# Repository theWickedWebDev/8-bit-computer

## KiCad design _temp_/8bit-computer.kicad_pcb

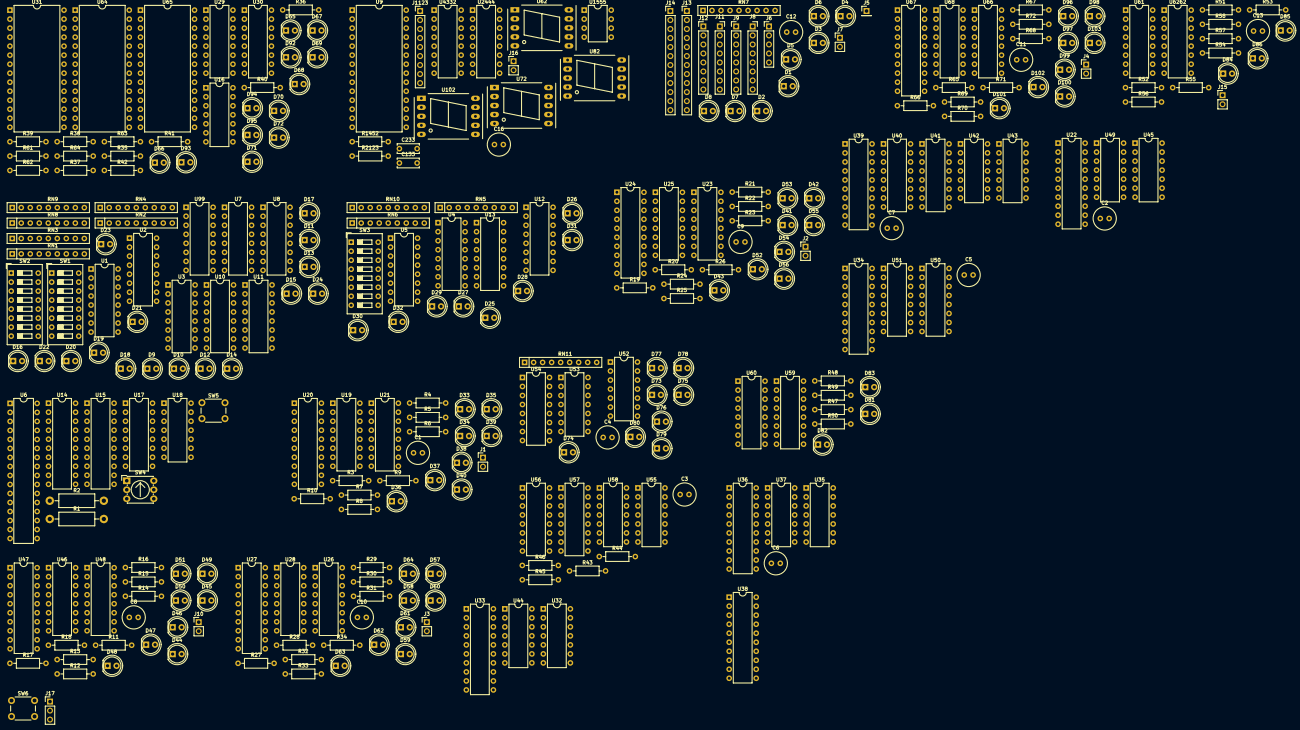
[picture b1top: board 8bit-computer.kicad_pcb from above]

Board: 2 copper layers, 296 parts (0 on the bottom side), 467 nets, no tracks yet.

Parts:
C1, C2, C3, C4, C5, C6, C7, C8, C9, C10, C11, C12, C13, C16: CP1; C_Radial_D6.3mm_H11.0mm_P2.50mm
C133: CP; C_Disc_D6.0mm_W2.5mm_P5.00mm
C233: C; C_Disc_D6.0mm_W2.5mm_P5.00mm
D1, D2, D3, D4, D5, D6, D7, D8, D9, D10, D11, D12, D13, D14, D15, D16, D17, D18, D19, D20, D21, D22, D23, D24, D25, D26, D27, D28, D29, D30, D31, D32, D33, D34, D35, D36, D37, D38, D39, D40, D41, D42, D43, D44, D45, D46, D47, D48, D49, D50, D51, D52, D53, D54, D55, D56, D57, D58, D59, D60, D61, D62, D63, D64, D65, D66, D67, D68, D69, D70, D71, D72, D73, D74, D75, D76, D77, D78, D79, D80, D81, D82, D83, D84, D85, D86, D92, D93, D94, D95, D96, D97, D98, D99, D100, D101, D102, D103: LED; LED_D5.0mm
J1, J2, J3, J4, J7, J10, J15, J16: Conn_01x04; PinHeader_1x02_P2.54mm_Vertical
J5: Conn_01x04; PinHeader_1x01_P2.54mm_Vertical
J6: Conn_01x04; PinHeader_1x05_P2.54mm_Vertical
J8, J11: Conn_01x08; PinSocket_1x08_P2.54mm_Vertical
J9, J12: Conn_01x08; PinHeader_1x08_P2.54mm_Vertical
J13, J14: Conn_01x08; PinHeader_1x12_P2.54mm_Vertical
J17: Conn_01x03; PinHeader_1x03_P2.54mm_Vertical
J1123: Conn_01x09; PinHeader_1x09_P2.54mm_Vertical
R1, R2: R_US; R_Axial_DIN0411_L9.9mm_D3.6mm_P15.24mm_Horizontal
R3, R4, R5, R6, R7, R8, R9, R10, R11, R12, R13, R14, R15, R16, R17, R18, R19, R20, R21, R22, R23, R24, R25, R26, R27, R28, R29, R30, R31, R32, R33, R34, R35, R36, R37, R38, R39, R40, R41, R42, R43, R44, R45, R46, R47, R48, R49, R50, R51, R52, R53, R54, R55, R56, R57, R58, R61, R62, R63, R64, R65, R66, R67, R68, R69, R70, R71, R72, R1452, R2123: R_US; R_Axial_DIN0207_L6.3mm_D2.5mm_P10.16mm_Horizontal
RN1, RN2, RN3, RN4, RN5, RN6, RN8, RN9, RN10: R_Network08_US; R_Array_SIP9
RN7, RN11: R_Network08; R_Array_SIP9
SW1, SW2, SW3: SW_DIP_x08; SW_DIP_SPSTx08_Slide_9.78x22.5mm_W7.62mm_P2.54mm
SW4: SW_SPDT; Nidec_Copal_SH-7010C
SW5, SW6: SW_Push; SW_PUSH_6mm
U1, U2, U4, U5, U7, U10, U19, U21, U23, U25, U26, U28, U66, U68: 74LS173; DIP-16_W7.62mm
U3, U8, U11, U12, U13, U17, U56, U57, U99: 74LS157; DIP-16_W7.62mm
U6: IS61C1024-15N; DIP-32_W7.62mm
U9, U31, U64, U65: AT28C256; DIP-28_W15.24mm
U14, U15, U20, U22, U24, U27, U33, U34, U36, U38, U39, U47, U67: 74LS245; DIP-20_W7.62mm
U16, U52, U55, U58: 74LS04; DIP-14_W7.62mm
U18: 74LS00; DIP-14_W7.62mm
U29, U46, U48: 74LS161; DIP-16_W7.62mm
U30, U54: 74LS138; DIP-16_W7.62mm
U32, U44, U53: 74LS08; DIP-14_W7.62mm
U35, U37, U42, U43: 74LS86; DIP-14_W7.62mm
U40, U41: 74LS283; DIP-16_W7.62mm
U45, U49: 74LS32; DIP-14_W7.62mm
U50, U51: 74LS194; DIP-16_W7.62mm
U59, U60: 74LS85; DIP-16_W7.62mm
U61, U6262: 74LS08; DIP-16_W7.62mm
U62, U72, U82, U102: HDSP-7503; 7SegmentLED_LTS6760_LTS6780
U1555: NE55P; DIP-8_W7.62mm
U2444: 74LS76; DIP-16_W7.62mm
U4332: 74LS139; DIP-16_W7.62mm

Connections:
+5V: R1.1, R2.2, RN1.1, RN2.1, RN3.1, RN4.1, RN6.1, U1.16, U2.16, U3.16, U4.16, U5.16, U6.30, U6.32, U7.16, U8.16, U10.16, U11.16, U12.16, U13.16, U14.20, U15.20, U17.16, U99.16
/ALU Arithmetic Logic Unit/A1: J8.8, J9.8, U37.13, U38.11, U41.5, U44.1, U49.12, U51.6, U59.10
/ALU Arithmetic Logic Unit/A2: J8.7, J9.7, U37.10, U38.12, U41.3, U44.4, U49.9, U51.5, U59.12
/ALU Arithmetic Logic Unit/A3: J8.6, J9.6, U37.5, U38.13, U41.14, U44.9, U49.4, U51.4, U59.13
/ALU Arithmetic Logic Unit/A4: J8.5, J9.5, U37.2, U38.14, U41.12, U44.12, U49.1, U51.3, U59.15
/ALU Arithmetic Logic Unit/A5: J8.4, J9.4, U32.1, U35.13, U38.15, U40.5, U45.12, U50.6, U60.10
/ALU Arithmetic Logic Unit/A6: J8.3, J9.3, U32.4, U35.10, U38.16, U40.3, U45.9, U50.5, U60.12
/ALU Arithmetic Logic Unit/A7: J8.2, J9.2, U32.9, U35.5, U38.17, U40.14, U45.4, U50.4, U60.13
/ALU Arithmetic Logic Unit/A8: J8.1, J9.1, U32.12, U35.2, U38.18, U40.12, U45.1, U50.3, U60.15
/ALU Arithmetic Logic Unit/ALU Control Pins/ADD: U39.19, U53.3
/ALU Arithmetic Logic Unit/ALU Control Pins/AND: D77.2, U33.19, U54.12
/ALU Arithmetic Logic Unit/ALU Control Pins/EN: J6.2, U54.6
/ALU Arithmetic Logic Unit/ALU Control Pins/F0: J6.5, U54.1
/ALU Arithmetic Logic Unit/ALU Control Pins/F1: J6.4, U54.2
/ALU Arithmetic Logic Unit/ALU Control Pins/F2: J6.3, U54.3
/ALU Arithmetic Logic Unit/ALU Control Pins/SHIFT_EN: U34.19, U53.6
/ALU Arithmetic Logic Unit/ALU Control Pins/SHL: D75.2, U50.10, U51.10, U53.4, U54.10
/ALU Arithmetic Logic Unit/ALU Control Pins/SHR: D74.2, U50.9, U51.9, U53.5, U54.9
/ALU Arithmetic Logic Unit/B1: J11.8, J12.8, U37.12, U43.12, U44.2, U49.13, U59.9
/ALU Arithmetic Logic Unit/B2: J11.7, J12.7, U37.9, U43.9, U44.5, U49.10, U59.11
/ALU Arithmetic Logic Unit/B3: J11.6, J12.6, U37.4, U43.4, U44.10, U49.5, U59.14
/ALU Arithmetic Logic Unit/B4: J11.5, J12.5, U37.1, U43.1, U44.13, U49.2, U59.1
/ALU Arithmetic Logic Unit/B5: J11.4, J12.4, U32.2, U35.12, U42.12, U45.13, U60.9
/ALU Arithmetic Logic Unit/B6: J11.3, J12.3, U32.5, U35.9, U42.9, U45.10, U60.11
/ALU Arithmetic Logic Unit/B7: J11.2, J12.2, U32.10, U35.4, U42.4, U45.5, U60.14
/ALU Arithmetic Logic Unit/B8: J11.1, J12.1, U32.13, U35.1, U42.1, U45.2, U60.1
/ALU Arithmetic Logic Unit/CARRY: J13.12, J14.12, U40.9, U61.12
/ALU Arithmetic Logic Unit/Compare Unit (GT, LT, EQ)/GT: D83.2, J13.9, J14.9, U60.5
/ALU Arithmetic Logic Unit/Compare Unit (GT, LT, EQ)/LT: D82.2, J13.10, J14.10, U60.7
/ALU Arithmetic Logic Unit/EQ: D81.2, J13.11, J14.11, U60.6, U6262.2
/ALU Arithmetic Logic Unit/NOT Unit/ALU_OUT1: D8.2, J13.1, J14.1, U57.4
/ALU Arithmetic Logic Unit/NOT Unit/ALU_OUT2: D7.2, J13.2, J14.2, U57.7
/ALU Arithmetic Logic Unit/NOT Unit/ALU_OUT3: D6.2, J13.3, J14.3, U57.9
/ALU Arithmetic Logic Unit/NOT Unit/ALU_OUT4: D5.2, J13.4, J14.4, U57.12
/ALU Arithmetic Logic Unit/NOT Unit/ALU_OUT5: D4.2, J13.5, J14.5, U56.4
/ALU Arithmetic Logic Unit/NOT Unit/ALU_OUT6: D3.2, J13.6, J14.6, U56.7
/ALU Arithmetic Logic Unit/NOT Unit/ALU_OUT7: D2.2, J13.7, J14.7, U56.9
/ALU Arithmetic Logic Unit/NOT Unit/ALU_OUT8: D1.2, J13.8, J14.8, U56.12
/ALU Arithmetic Logic Unit/NOT Unit/INVERT: J6.1, U56.1, U57.1
/ALU Arithmetic Logic Unit/OR Unit/OE: D78.2, U22.19, U54.13
/ALU Arithmetic Logic Unit/Pass Through Unit/OE: D73.2, U38.19, U54.7
/ALU Arithmetic Logic Unit/SUB: U41.7, U42.2, U42.5, U42.10, U42.13, U43.2, U43.5, U43.10, U43.13, U52.2
/ALU Arithmetic Logic Unit/SUM_HIGH_BIT: U22.2, U33.2, U34.2, U36.2, U38.2, U39.2, U55.1, U56.14, U6262.4
/ALU Arithmetic Logic Unit/Shift Left/Right Unit/CLOCK: J5.1, U50.11, U51.11
/ALU Arithmetic Logic Unit/XOR Unit/OE: D76.2, U36.19, U54.11
/ALU Arithmetic Logic Unit/Y1: U22.9, U33.9, U34.9, U36.9, U38.9, U39.9, U52.3, U57.2
/ALU Arithmetic Logic Unit/Y2: U22.8, U33.8, U34.8, U36.8, U38.8, U39.8, U57.5, U58.1
/ALU Arithmetic Logic Unit/Y3: U16.13, U22.7, U33.7, U34.7, U36.7, U38.7, U39.7, U57.11
/ALU Arithmetic Logic Unit/Y4: U16.11, U22.6, U33.6, U34.6, U36.6, U38.6, U39.6, U57.14
/ALU Arithmetic Logic Unit/Y5: U16.9, U22.5, U33.5, U34.5, U36.5, U38.5, U39.5, U56.2
/ALU Arithmetic Logic Unit/Y6: U16.5, U22.4, U33.4, U34.4, U36.4, U38.4, U39.4, U56.5
/ALU Arithmetic Logic Unit/Y7: U16.3, U22.3, U33.3, U34.3, U36.3, U38.3, U39.3, U56.11
/CLOCK: J17.1, U1.7, U2.7, U4.7, U5.7, U7.7, U10.7, U18.2, U19.7, U21.7, U23.7, U25.7, U26.7, U28.7, U29.2, U46.2, U48.2, U61.7, U66.7, U68.7
/Clock/HALT: J17.2, U65.18
/Control Word Unit/FLAG1: U31.7, U64.7, U65.7
/Control Word Unit/FLAG2: U31.6, U64.6, U65.6
/Control Word Unit/FLAG3: U31.5, U64.5, U65.5
/Control Word Unit/FLAG4: U31.4, U64.4, U65.4
/Control Word Unit/INST1: U31.3, U64.3, U65.3, U67.2
/Control Word Unit/INST2: U31.25, U64.25, U65.25, U67.3
/Control Word Unit/INST3: U31.24, U64.24, U65.24, U67.4
/Control Word Unit/INST4: U31.21, U64.21, U65.21, U67.5
/Control Word Unit/INST5: U31.23, U64.23, U65.23, U67.6
/Control Word Unit/INST6: U31.2, U64.2, U65.2, U67.7
/Control Word Unit/INST7: U31.26, U64.26, U65.26, U67.8
/Control Word Unit/INST8: U31.1, U64.1, U65.1, U67.9
/Control Word Unit/MAR1_LATCH: U1.9, U1.10, U2.9, U2.10, U65.11
/Control Word Unit/MAR2_LATCH: U7.9, U7.10, U10.9, U10.10, U31.19
/Control Word Unit/MC18: U65.12, U66.9, U66.10, U68.9, U68.10
/Control Word Unit/MC19: U65.13, U67.19
/Control Word Unit/MEM_DATA_LATCH: U4.9, U4.10, U5.9, U5.10, U31.17
/Control Word Unit/RAM_MODE: SW4.2, U3.1, U8.1, U11.1, U12.1, U13.1, U17.1, U99.1
/Control Word Unit/RAM_OUT: U15.19, U31.18
/Control Word Unit/RAM_WRITE: U14.19, U16.2, U18.1, U31.16
/Control Word Unit/REGISTER_A_IN: U19.9, U19.10, U21.9, U21.10, U31.11
/Control Word Unit/REGISTER_A_OUT: U20.19, U64.19
/Control Word Unit/REGISTER_B_IN: U23.9, U23.10, U25.9, U25.10, U64.18
/Control Word Unit/REGISTER_B_OUT: U24.19, U64.17
/Control Word Unit/REGISTER_SCRATCH_IN: U26.9, U26.10, U28.9, U28.10, U31.13
/Control Word Unit/REGISTER_SCRATCH_OUT: U27.19, U31.12
/Control Word Unit/RESET: U19.15, U21.15, U23.15, U25.15, U26.15, U28.15, U46.1, U48.1, U61.15, U65.19
/Control Word Unit/STEP1: D68.2, U29.14, U30.1, U31.10, U64.10, U65.10
/Control Word Unit/STEP2: D67.2, U29.13, U30.2, U31.9, U64.9, U65.9
/Control Word Unit/STEP3: D66.2, U29.12, U30.3, U31.8, U64.8, U65.8
/Control Word Unit/T0: D95.2, U30.15
/Control Word Unit/T1: D94.2, U30.14
/Control Word Unit/T2: D93.2, U30.13
/Control Word Unit/T3: D92.2, U30.12
/Control Word Unit/T4: D72.2, U30.11
/Control Word Unit/T5: D71.2, U30.10
/Control Word Unit/T6: D70.2, U30.9
/Control Word Unit/T7: D69.2, U30.7
/Counter Unit/JUMP: U46.9, U48.9
/Counter Unit/OE: U47.19, U65.15
/Display/A: U9.11, U62.10, U72.10, U82.10, U102.10
/Display/B: U9.12, U62.9, U72.9, U82.9, U102.9
/Display/C: U9.13, U62.8, U72.8, U82.8, U102.8
/Display/CLOCK_DISPLAY: U1555.3, U2444.6
/Display/D: U9.15, U62.5, U72.5, U82.5, U102.5
/Display/DP: U62.7, U72.7, U82.7, U102.7
/Display/E: U9.16, U62.4, U72.4, U82.4, U102.4
/Display/F: U9.17, U62.2, U72.2, U82.2, U102.2
/Display/G: U9.18, U62.3, U72.3, U82.3, U102.3
/Flags Register Unit/CARRY: D84.2, U61.5
/Flags Register Unit/LATCH: U31.15, U61.9, U61.10
/Flags Register Unit/NEG: D85.2, U61.4
/Flags Register Unit/SUB_IN: U6262.1, U6262.5
/Flags Register Unit/ZE: D86.2, U61.3
/Memory Address Register/MAR1: D24.2, U3.4, U6.12
/Memory Address Register/MAR2: D23.2, U3.7, U6.11
/Memory Address Register/MAR3: D22.2, U3.9, U6.10
/Memory Address Register/MAR4: D21.2, U3.12, U6.9
/Memory Address Register/MAR5: D20.2, U6.8, U8.4
/Memory Address Register/MAR7: D18.2, U6.6, U8.9
/Memory Address Register/MAR8: D17.2, U6.5, U8.12
/Memory Address Register/MAR9: D16.2, U6.27, U99.4
/Memory Address Register/MAR10: D15.2, U6.26, U99.7
/Memory Address Register/MAR11: D14.2, U6.23, U99.9
/Memory Address Register/MAR12: D13.2, U6.25, U99.12
/Memory Address Register/MAR13: D12.2, U6.4, U11.4
/Memory Address Register/MAR14: D11.2, U6.28, U11.7
/Memory Address Register/MAR15: D10.2, D19.2, U6.3, U6.7, U8.7, U11.9
/Memory Address Register/MAR16: D9.2, U6.31, U11.12
/Memory Address Register/RAM_RESET: U1.15, U2.15, U7.15, U10.15
/Memory Data Register/MEM_DATA_REG1: D32.2, U12.4
/Memory Data Register/MEM_DATA_REG2: D31.2, U12.7
/Memory Data Register/MEM_DATA_REG3: D30.2, U12.9
/Memory Data Register/MEM_DATA_REG4: D29.2, U12.12
/Memory Data Register/MEM_DATA_REG5: D28.2, U13.4
/Memory Data Register/MEM_DATA_REG6: D27.2, U13.7
/Memory Data Register/MEM_DATA_REG7: D26.2, U13.9
/Memory Data Register/MEM_DATA_REG8: D25.2, U13.12
/Memory Data Register/RAM_RESET: U4.15, U5.15
BUS1: U1.14, U4.14, U7.14, U15.2, U20.2, U21.14, U24.2, U25.14, U27.2, U28.14, U47.2, U48.3, U68.14
BUS2: U1.13, U4.13, U7.13, U15.3, U20.3, U21.13, U24.3, U25.13, U27.3, U28.13, U47.3, U48.4, U68.13
BUS3: U1.12, U4.12, U7.12, U15.4, U20.4, U21.12, U24.4, U25.12, U27.4, U28.12, U47.4, U48.5, U68.12
BUS4: U1.11, U4.11, U7.11, U15.5, U20.5, U21.11, U24.5, U25.11, U27.5, U28.11, U47.5, U48.6, U68.11
BUS5: U2.14, U5.14, U10.14, U15.6, U19.14, U20.6, U23.14, U24.6, U26.14, U27.6, U46.3, U47.6, U66.14
BUS6: U2.13, U5.13, U10.13, U15.7, U19.13, U20.7, U23.13, U24.7, U26.13, U27.7, U46.4, U47.7, U66.13
BUS7: U2.12, U5.12, U10.12, U15.8, U19.12, U20.8, U23.12, U24.8, U26.12, U27.8, U46.5, U47.8, U66.12
BUS8: U2.11, U5.11, U10.11, U15.9, U19.11, U20.9, U23.11, U24.9, U26.11, U27.9, U46.6, U47.9, U66.11
GND: C1.2, C2.2, C3.2, C4.2, C5.2, C6.2, C7.2, C8.2, C9.2, C10.2, C11.2, C12.2, C13.2, C16.2, C133.1, C233.2, J1.2, J2.2, J3.2, J4.2, J7.2, J10.2, J15.2, J16.2, R3.2, R4.2, R5.2, R6.2, R7.2, R8.2, R9.2, R10.2, R11.2, R12.2, R13.2, R14.2, R15.2, R16.2, R17.2, R18.2, R19.2, R20.2, R21.2, R22.2, R23.2, R24.2, R25.2, R26.2, R27.2, R28.2, R29.2, R30.2, R31.2, R32.2, R33.2, R34.2, R35.2, R36.2, R37.2, R38.2, R39.2, R40.2, R41.2, R42.2, R43.1, R44.1, R45.1, R46.1, R48.2, R49.2, R50.2, R51.2, R52.2, R53.2, R54.2, R55.2, R56.2, R57.2, R58.2, R61.2, R62.2, R63.2, R64.2, R65.2, R66.2, R67.2, R68.2, R69.2, R70.2, R71.2, R72.2, RN5.1, RN7.1, RN10.1, RN11.1, SW5.1, U1.1, U1.2, U1.8, U2.1, U2.2, U2.8, U3.8, U3.15, U4.1, U4.2, U4.8, U5.1, U5.2, U5.8, U6.2, U6.16, U6.22, U6.24, U7.1, U7.2, U7.8, U8.8, U8.15, U9.1, U9.2, U9.14, U9.20, U9.22, U9.23, U9.26, U10.1, U10.2, U10.8, U11.8, U11.15, U12.8, U12.15, U13.8, U13.15, U14.1, U14.10, U15.1, U15.10, U16.7, U17.8, U17.15, U19.1, U19.2, U19.8, U20.1, U20.10, U21.1, U21.2, U21.8, U22.1, U22.10, U23.1, U23.2, U23.8, U24.1, U24.10, U25.1, U25.2, U25.8, U26.1, U26.2, U26.8, U27.1, U27.10, U28.1, U28.2, U28.8, U29.8, U30.4, U30.5, U30.8, U31.14, U31.20, U31.22, U32.7, U33.1, U33.10, U34.1, U34.10, U35.7, U36.1, U36.10, U37.7, U38.1, U38.10, U39.1, U39.10, U40.8, U41.8, U42.7, U43.7, U44.7, U45.7, U46.8, U47.1, U47.10, U48.8, U49.7, U50.2, U50.8, U51.7, U51.8, U52.7, U53.7, U54.4, U54.5, U54.8, U55.7, U56.8, U56.15, U57.8, U57.15, U59.2, U59.4, U59.8, U60.8, U61.1, U61.2, U61.8, U61.11, U64.14, U64.20, U64.22, U65.14, U65.20, U65.22, U66.1, U66.2, U66.8, U66.15, U67.1, U67.10, U68.1, U68.2, U68.8, U68.15, U99.8, U99.15, U1555.1, U2444.13, U4332.1, U4332.8, U6262.7
unnamed: C1.1, J1.1
unnamed: C8.1, J10.1
unnamed: C9.1, J2.1
unnamed: C10.1, J3.1
unnamed: C11.1, J4.1
unnamed: C12.1, J7.1
unnamed: C13.1, J15.1
unnamed: C133.2, U1555.2
unnamed: C233.1, U1555.5
unnamed: D1.1, RN7.9
unnamed: D2.1, RN7.8
unnamed: D3.1, RN7.7
unnamed: D4.1, RN7.6
unnamed: D5.1, RN7.5
unnamed: D6.1, RN7.4
unnamed: D7.1, RN7.3
unnamed: D8.1, RN7.2
unnamed: D9.1, RN8.9
unnamed: D10.1, RN8.8
unnamed: D11.1, RN8.7
unnamed: D12.1, RN8.6
unnamed: D13.1, RN8.5
unnamed: D14.1, RN8.4
unnamed: D15.1, RN8.3
unnamed: D16.1, RN8.2
unnamed: D17.1, RN9.9
unnamed: D18.1, RN9.8
unnamed: D19.1, RN9.7
unnamed: D20.1, RN9.6
unnamed: D21.1, RN9.5
unnamed: D22.1, RN9.4
unnamed: D23.1, RN9.3
unnamed: D24.1, RN9.2
unnamed: D25.1, RN10.9
unnamed: D26.1, RN10.8
unnamed: D27.1, RN10.7
unnamed: D28.1, RN10.6
unnamed: D29.1, RN10.5
unnamed: D30.1, RN10.4
unnamed: D31.1, RN10.3
unnamed: D32.1, RN10.2
unnamed: D33.1, R3.1
unnamed: D33.2, U19.6, U20.18
unnamed: D34.1, R4.1
unnamed: D34.2, U19.5, U20.17
unnamed: D35.1, R5.1
unnamed: D35.2, U19.4, U20.16
unnamed: D36.1, R6.1
unnamed: D36.2, U19.3, U20.15
unnamed: D37.1, R7.1
unnamed: D37.2, U20.14, U21.6
unnamed: D38.1, R8.1
unnamed: D38.2, U20.13, U21.5
unnamed: D39.1, R9.1
unnamed: D39.2, U20.12, U21.4
unnamed: D40.1, R10.1
unnamed: D40.2, U20.11, U21.3
unnamed: D41.1, R19.1
unnamed: D41.2, U23.6, U24.18
unnamed: D42.1, R20.1
unnamed: D42.2, U23.5, U24.17
unnamed: D43.1, R21.1
unnamed: D43.2, U23.4, U24.16
unnamed: D44.1, R11.1
unnamed: D44.2, U46.11, U47.18
unnamed: D45.1, R12.1
unnamed: D45.2, U46.12, U47.17
unnamed: D46.1, R13.1
unnamed: D46.2, U46.13, U47.16
unnamed: D47.1, R14.1
unnamed: D47.2, U46.14, U47.15
unnamed: D48.1, R15.1
unnamed: D48.2, U47.14, U48.11
unnamed: D49.1, R16.1
unnamed: D49.2, U47.13, U48.12
unnamed: D50.1, R17.1
unnamed: D50.2, U47.12, U48.13
unnamed: D51.1, R18.1
unnamed: D51.2, U47.11, U48.14
unnamed: D52.1, R22.1
unnamed: D52.2, U23.3, U24.15
unnamed: D53.1, R23.1
unnamed: D53.2, U24.14, U25.6
unnamed: D54.1, R24.1
unnamed: D54.2, U24.13, U25.5
unnamed: D55.1, R25.1
unnamed: D55.2, U24.12, U25.4
unnamed: D56.1, R26.1
unnamed: D56.2, U24.11, U25.3
unnamed: D57.1, R27.1
unnamed: D57.2, U26.6, U27.18
unnamed: D58.1, R28.1
unnamed: D58.2, U26.5, U27.17
unnamed: D59.1, R29.1
unnamed: D59.2, U26.4, U27.16
unnamed: D60.1, R30.1
unnamed: D60.2, U26.3, U27.15
unnamed: D61.1, R31.1
unnamed: D61.2, U27.14, U28.6
unnamed: D62.1, R32.1
unnamed: D62.2, U27.13, U28.5
unnamed: D63.1, R33.1
unnamed: D63.2, U27.12, U28.4
unnamed: D64.1, R34.1
unnamed: D64.2, U27.11, U28.3
unnamed: D65.1, R35.1
unnamed: D65.2, U29.11
unnamed: D66.1, R36.1
unnamed: D67.1, R37.1
unnamed: D68.1, R38.1
unnamed: D69.1, R39.1
unnamed: D70.1, R40.1
unnamed: D71.1, R41.1
unnamed: D72.1, R42.1
unnamed: D73.1, RN11.9
unnamed: D74.1, RN11.8
unnamed: D75.1, RN11.7
unnamed: D76.1, RN11.6
unnamed: D77.1, RN11.5
unnamed: D78.1, RN11.4
unnamed: D79.1, RN11.3
unnamed: D79.2, U52.1, U53.2, U54.14
unnamed: D80.1, RN11.2
unnamed: D80.2, U53.1, U54.15
unnamed: D81.1, R48.1
unnamed: D82.1, R49.1
unnamed: D83.1, R50.1
unnamed: D84.1, R52.1
unnamed: D85.1, R53.1
unnamed: D86.1, R54.1
unnamed: D92.1, R61.1
unnamed: D93.1, R62.1
unnamed: D94.1, R63.1
unnamed: D95.1, R64.1
unnamed: D96.1, R65.1
unnamed: D96.2, U66.6, U67.18
unnamed: D97.1, R66.1
unnamed: D97.2, U66.5, U67.17
unnamed: D98.1, R67.1
unnamed: D98.2, U66.4, U67.16
unnamed: D99.1, R68.1
unnamed: D99.2, U66.3, U67.15
unnamed: D100.1, R69.1
unnamed: D100.2, U67.14, U68.6
unnamed: D101.1, R70.1
unnamed: D101.2, U67.13, U68.5
unnamed: D102.1, R71.1
unnamed: D102.2, U67.12, U68.4
unnamed: D103.1, R72.1
unnamed: D103.2, U67.11, U68.3
unnamed: J17.3, SW6.1
unnamed: J1123.1, U9.21
unnamed: J1123.2, U9.3
unnamed: J1123.3, U9.4
unnamed: J1123.4, U9.5
unnamed: J1123.5, U9.6
unnamed: J1123.6, U9.7
unnamed: J1123.7, U9.8
unnamed: J1123.8, U9.9
unnamed: J1123.9, U9.10
unnamed: R1.2, SW4.1
unnamed: R2.1, SW5.2, U17.13
unnamed: R43.2, U52.5
unnamed: R44.2, U52.9
unnamed: R45.2, U52.11
unnamed: R46.2, U52.13
unnamed: R47.2, U59.3
unnamed: R51.1, U61.6
unnamed: R55.1, U6262.10
unnamed: R56.1, U6262.9
unnamed: R57.1, U6262.13
unnamed: R58.1, U6262.12
unnamed: R1452.1, R2123.1, U1555.7
unnamed: R1452.2, U1555.6
unnamed: RN1.2, SW1.8, U99.3
unnamed: RN1.3, SW1.7, U99.6
unnamed: RN1.4, SW1.6, U99.10
unnamed: RN1.5, SW1.5, U99.13
unnamed: RN1.6, SW1.4, U11.3
unnamed: RN1.7, SW1.3, U11.6
unnamed: RN1.8, SW1.2, U11.10
unnamed: RN1.9, SW1.1, U11.13
unnamed: RN2.2, SW1.16
unnamed: RN2.3, SW1.15
unnamed: RN2.4, SW1.14
unnamed: RN2.5, SW1.13
unnamed: RN2.6, SW1.12
unnamed: RN2.7, SW1.11
unnamed: RN2.8, SW1.10
unnamed: RN2.9, SW1.9
unnamed: RN3.2, SW2.8, U3.3
unnamed: RN3.3, SW2.7, U3.6
unnamed: RN3.4, SW2.6, U3.10
unnamed: RN3.5, SW2.5, U3.13
unnamed: RN3.6, SW2.4, U8.3
unnamed: RN3.7, SW2.3, U8.6
unnamed: RN3.8, SW2.2, U8.10
unnamed: RN3.9, SW2.1, U8.13
unnamed: RN4.2, SW2.16
unnamed: RN4.3, SW2.15
unnamed: RN4.4, SW2.14
unnamed: RN4.5, SW2.13
unnamed: RN4.6, SW2.12
unnamed: RN4.7, SW2.11
unnamed: RN4.8, SW2.10
unnamed: RN4.9, SW2.9
unnamed: RN5.2, SW3.8, U12.3
unnamed: RN5.3, SW3.7, U12.6
unnamed: RN5.4, SW3.6, U12.10
unnamed: RN5.5, SW3.5, U12.13
unnamed: RN5.6, SW3.4, U13.3
unnamed: RN5.7, SW3.3, U13.6
unnamed: RN5.8, SW3.2, U13.10
unnamed: RN5.9, SW3.1, U13.13
unnamed: RN6.2, SW3.16
unnamed: RN6.3, SW3.15
unnamed: RN6.4, SW3.14
unnamed: RN6.5, SW3.13
unnamed: RN6.6, SW3.12
unnamed: RN6.7, SW3.11
unnamed: RN6.8, SW3.10
unnamed: RN6.9, SW3.9
unnamed: U1.3, U3.2
unnamed: U1.4, U3.5
unnamed: U1.5, U3.11
unnamed: U1.6, U3.14
unnamed: U2.3, U8.2
unnamed: U2.4, U8.5
unnamed: U2.5, U8.11
unnamed: U2.6, U8.14
unnamed: U7.3, U99.2
unnamed: U7.4, U99.5
unnamed: U7.5, U99.11
unnamed: U7.6, U99.14
unnamed: U10.3, U11.2
unnamed: U10.4, U11.5
unnamed: U10.5, U11.11
unnamed: U10.6, U11.14
unnamed: U4.3, U12.2
unnamed: U4.4, U12.5
unnamed: U4.5, U12.11
unnamed: U4.6, U12.14
unnamed: U5.3, U13.2
unnamed: U5.4, U13.5
unnamed: U5.5, U13.11
unnamed: U5.6, U13.14
unnamed: U6.13, U14.2, U15.18
unnamed: U6.14, U14.3, U15.17
unnamed: U6.15, U14.4, U15.16
unnamed: U6.17, U14.5, U15.15
unnamed: U6.18, U14.6, U15.14
unnamed: U6.19, U14.7, U15.13
unnamed: U6.20, U14.8, U15.12
unnamed: U6.21, U14.9, U15.11
unnamed: U16.4, U56.10
unnamed: U16.6, U56.6
unnamed: U16.8, U56.3
unnamed: U16.10, U57.13
unnamed: U16.12, U57.10
unnamed: U6.29, U17.12
unnamed: U17.14, U18.3
unnamed: U22.11, U49.11
unnamed: U22.12, U49.8
unnamed: U22.13, U49.6
unnamed: U22.14, U49.3
unnamed: U22.15, U45.11
unnamed: U22.16, U45.8
unnamed: U22.17, U45.6
unnamed: U22.18, U45.3
unnamed: U32.3, U33.15
unnamed: U32.6, U33.16
unnamed: U32.8, U33.17
unnamed: U32.11, U33.18
unnamed: U33.11, U44.3
unnamed: U33.12, U44.6
unnamed: U33.13, U44.8
unnamed: U33.14, U44.11
unnamed: U34.11, U51.12
unnamed: U34.12, U51.13
unnamed: U34.13, U51.14
unnamed: U34.14, U50.7, U51.15
unnamed: U34.15, U50.12, U51.2
unnamed: U34.16, U50.13
unnamed: U34.17, U50.14
unnamed: U34.18, U50.15
unnamed: U35.3, U36.18
unnamed: U35.6, U36.17
unnamed: U35.8, U36.16
unnamed: U35.11, U36.15
unnamed: U36.11, U37.11
unnamed: U36.12, U37.8
unnamed: U36.13, U37.6
unnamed: U36.14, U37.3
unnamed: U39.11, U41.4
unnamed: U39.12, U41.1
unnamed: U39.13, U41.13
unnamed: U39.14, U41.10
unnamed: U39.15, U40.4
unnamed: U39.16, U40.1
unnamed: U39.17, U40.13
unnamed: U39.18, U40.10
unnamed: U40.2, U42.8
unnamed: U40.6, U42.11
unnamed: U40.7, U41.9
unnamed: U40.11, U42.3
unnamed: U40.15, U42.6
unnamed: U41.2, U43.8
unnamed: U41.6, U43.11
unnamed: U41.11, U43.3
unnamed: U41.15, U43.6
unnamed: U46.10, U48.15
unnamed: U52.4, U57.3
unnamed: U55.2, U56.13
unnamed: U57.6, U58.2
unnamed: U59.5, U60.4
unnamed: U59.6, U60.3
unnamed: U59.7, U60.2
unnamed: U61.13, U6262.6
unnamed: U61.14, U6262.3
unnamed: U102.1, U102.6, U4332.4
unnamed: U9.25, U2444.1, U2444.10, U4332.2
unnamed: U82.1, U82.6, U4332.5
unnamed: U72.1, U72.6, U4332.6
unnamed: U62.1, U62.6, U4332.7
VCC: C2.1, C3.1, C4.1, C5.1, C6.1, C7.1, C16.1, J16.1, R47.1, R2123.2, SW6.2, U9.24, U9.27, U9.28, U16.14, U19.16, U20.20, U21.16, U22.20, U23.16, U24.20, U25.16, U26.16, U27.20, U28.16, U29.7, U29.9, U29.10, U29.16, U30.6, U30.16, U31.27, U31.28, U32.14, U33.20, U34.20, U35.14, U36.20, U37.14, U38.20, U39.20, U40.16, U41.16, U42.14, U43.14, U44.14, U45.14, U46.7, U46.16, U47.20, U48.7, U48.10, U48.16, U49.14, U50.1, U50.16, U51.1, U51.16, U52.14, U53.14, U54.16, U55.14, U56.16, U57.16, U59.16, U60.16, U61.16, U64.27, U64.28, U65.27, U65.28, U66.16, U67.20, U68.16, U1555.8, U2444.2, U2444.3, U2444.4, U2444.5, U2444.7, U2444.8, U2444.9, U2444.12, U2444.15, U2444.16, U4332.3, U4332.16, U6262.14

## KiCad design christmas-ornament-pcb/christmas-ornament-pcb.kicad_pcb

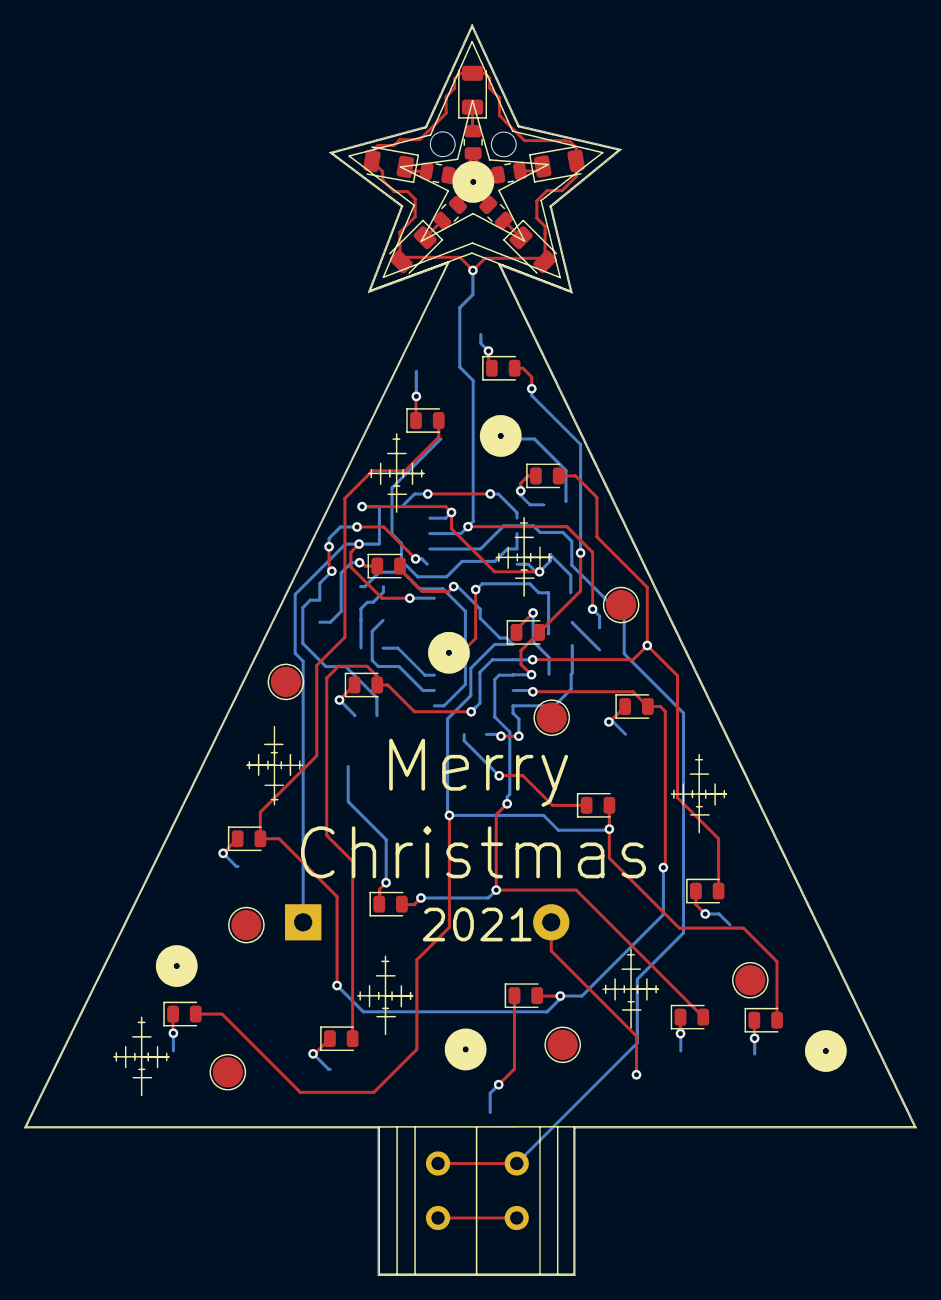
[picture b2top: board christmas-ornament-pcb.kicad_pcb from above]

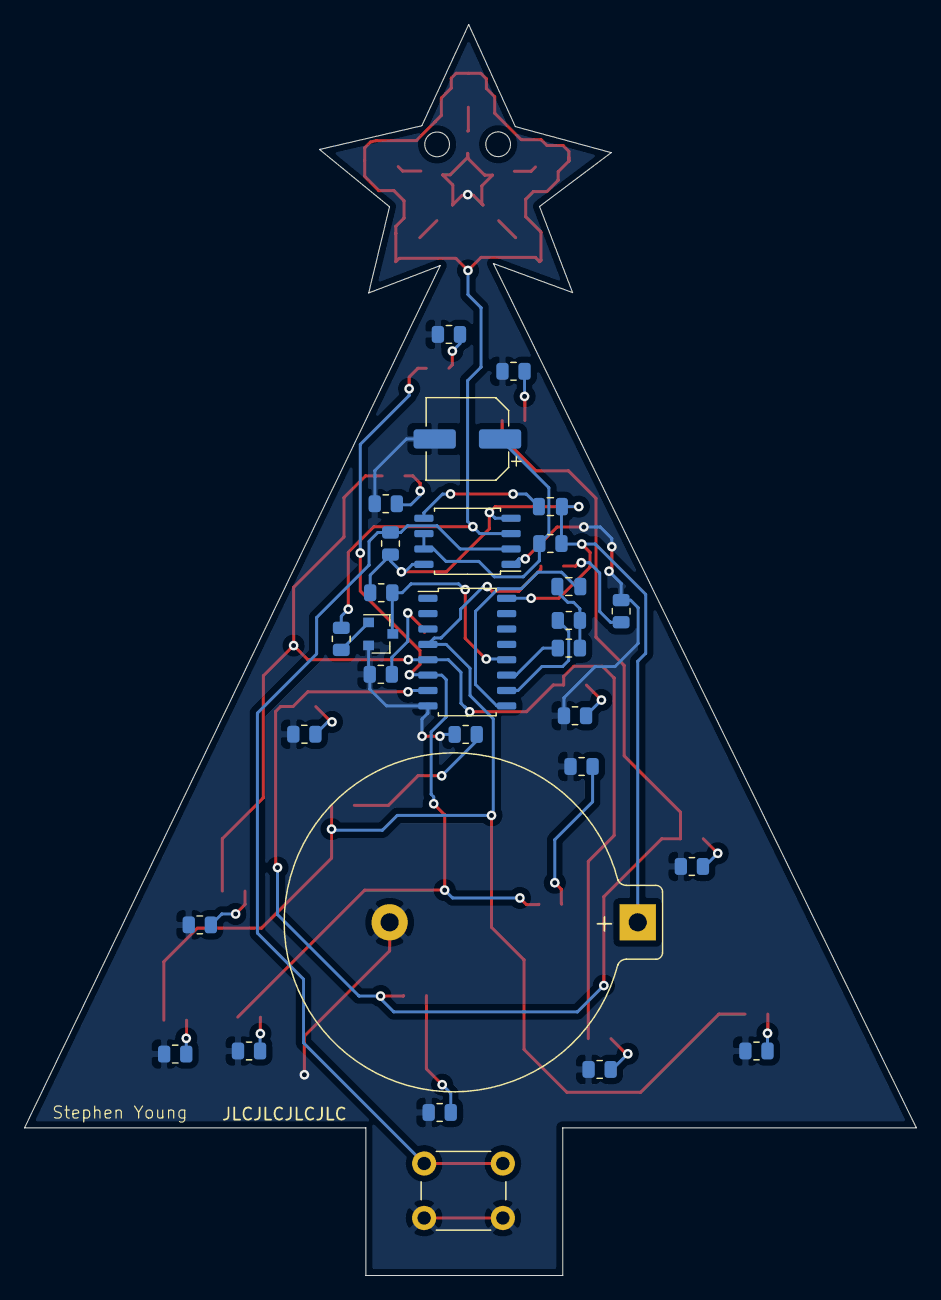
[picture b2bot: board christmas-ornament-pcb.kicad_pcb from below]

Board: 2 copper layers, 73.7 x 103.3 mm, 56 parts (30 on the bottom side), 37 nets.

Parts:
BT1: Battery_Cell; BatteryHolder_Keystone_105_1x2430
C1, C3: C; C_0805_2012Metric
C2: CP1; CP_Elec_6.3x5.8
D1, D2, D3, D4, D5, D6, D7, D8, D9, D10, D11, D12, D13, D14, D15, D16: LED; LED_0805_2012Metric
D17, D18, D19, D20, D21: LED; LED_1206_3216Metric
Q1: PMBT2222; SOT-23
R1, R4: 10kohm; R_0805_2012Metric
R2, R3, R5, R6, R7, R8, R9, R10, R11, R12, R13, R14, R15, R16, R17, R18, R19, R20, R21, R22, R23, R24, R25, R26, R27: 3.9kohm; R_0805_2012Metric
SW1: SW_Push; SW_PUSH_6mm
U1: LMC555xM; SOIC-8_5.23x5.23mm_P1.27mm
U2: CD4060; SOP-16_4.55x10.3mm_P1.27mm

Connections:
GND: BT1.2, C2.2, Q1.2, R7.2, R8.2, R9.2, R10.2, R11.2, R12.2, R13.2, R14.2, R15.2, R16.2, R17.2, R18.2, R19.2, R20.2, R21.2, R22.2, R23.2, R24.2, R25.2, R26.2, R27.2, SW1.1, U1.1, U2.8
unnamed: C1.1, U1.5
unnamed: C2.1, R4.2, U1.6, U1.7
unnamed: C3.1, U2.9
unnamed: C3.2, R5.2, R6.2
unnamed: D1.1, R7.1
unnamed: D1.2, D2.2, D3.2, D4.2, U2.7
unnamed: D2.1, R8.1
unnamed: D3.1, R9.1
unnamed: D4.1, R10.1
unnamed: D5.1, R11.1
unnamed: D5.2, D6.2, D7.2, D8.2, U2.5
unnamed: D6.1, R12.1
unnamed: D7.1, R13.1
unnamed: D8.1, R14.1
unnamed: D9.1, R15.1
unnamed: D10.1, R16.1
unnamed: D9.2, D10.2, D11.2, D12.2, U2.4
unnamed: D11.1, R17.1
unnamed: D12.1, R18.1
unnamed: D13.1, R19.1
unnamed: D13.2, D14.2, D15.2, D16.2, U2.6
unnamed: D14.1, R20.1
unnamed: D15.1, R21.1
unnamed: D16.1, R22.1
unnamed: D17.1, R23.1
unnamed: D17.2, D18.2, D19.2, D20.2, D21.2, R1.1, U1.3
unnamed: D18.1, R24.1
unnamed: D19.1, R25.1
unnamed: D20.1, R26.1
unnamed: D21.1, R27.1
unnamed: Q1.1, R1.2
unnamed: Q1.3, R2.1, U2.12
unnamed: R3.2, SW1.2, U1.2
unnamed: R5.1, U2.11
unnamed: R6.1, U2.10
VCC: BT1.1, C1.2, R2.2, R3.1, R4.1, U1.4, U1.8, U2.16

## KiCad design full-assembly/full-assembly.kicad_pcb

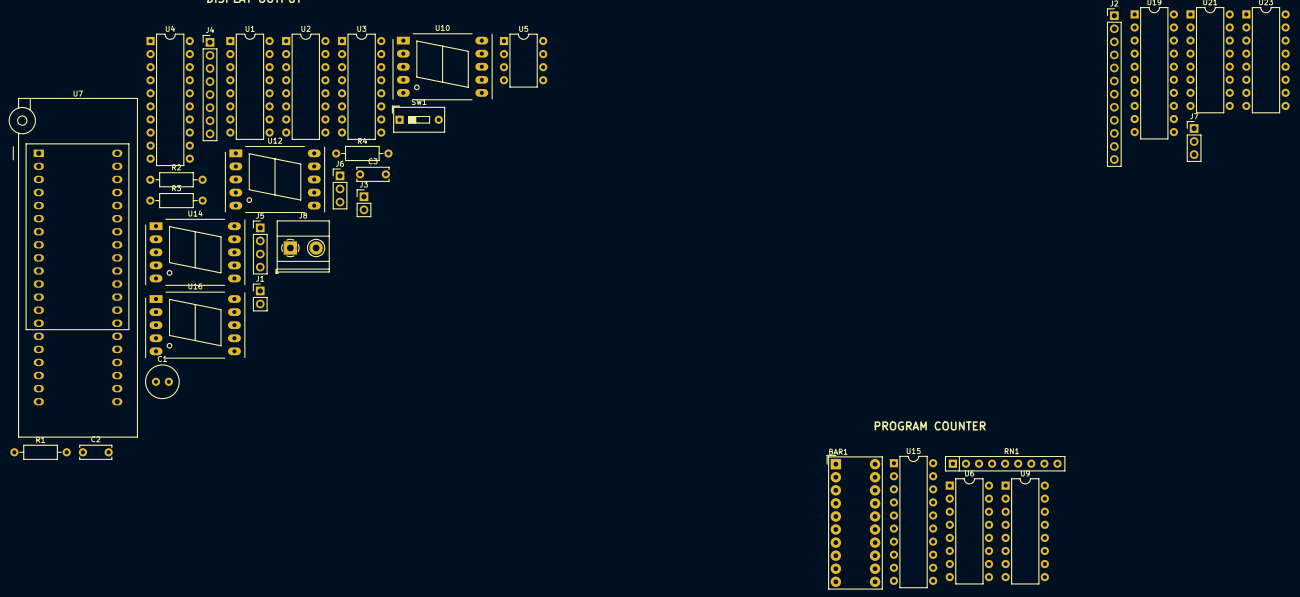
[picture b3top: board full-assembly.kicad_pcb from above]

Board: 2 copper layers, 34 parts (0 on the bottom side), 73 nets, no tracks yet.

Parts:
BAR1: HDSP-4830_2; HDSP-4830
C1: CP1; C_Radial_D6.3mm_H11.0mm_P2.50mm
C2: CP; C_Disc_D6.0mm_W2.5mm_P5.00mm
C3: C; C_Disc_D6.0mm_W2.5mm_P5.00mm
J1: Conn_01x04; PinHeader_1x02_P2.54mm_Vertical
J2: Conn_01x12; PinHeader_1x12_P2.54mm_Vertical
J3: Conn_01x02; PinHeader_1x02_P2.54mm_Vertical
J4: BUS; PinHeader_1x08_P2.54mm_Vertical
J5: Conn_01x04; PinHeader_1x04_P2.54mm_Vertical
J6, J7: Conn_01x03; PinHeader_1x03_P2.54mm_Vertical
J8: Screw_Terminal_01x02; TerminalBlock_Phoenix_MKDS-1,5-2_1x02_P5.00mm_Horizontal
R1, R2, R3, R4: R_US; R_Axial_DIN0207_L6.3mm_D2.5mm_P10.16mm_Horizontal
RN1: R_Network08; R_Array_SIP9
SW1: SW_SPST; SW_DIP_SPSTx01_Slide_9.78x4.72mm_W7.62mm_P2.54mm
U1: 74LS76; DIP-16_W7.62mm
U2: 74LS08; DIP-16_W7.62mm
U3: 74LS139; DIP-16_W7.62mm
U4: 74LS273; DIP-20_W7.62mm
U5: NE55P; DIP-8_W7.62mm
U6, U9: 74LS161; DIP-16_W7.62mm
U7: AT28C256; DIP_Socket-40_W11.9_W12.7_W15.24_W17.78_W18.5_3M_240-1280-0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
U10, U12, U14, U16: HDSP-7503; 7SegmentLED_LTS6760_LTS6780
U15, U19: 74LS245; DIP-20_W7.62mm
U21, U23: 74LS173; DIP-16_W7.62mm

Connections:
1_DISPLAY: U3.4, U16.3, U16.8
10_DISPLAY: U3.5, U14.3, U14.8
100_DISPLAY: U3.6, U12.3, U12.8
A_REGISTER_IN: J2.10, U21.9, U21.10, U23.9, U23.10
A_REGISTER_OUT: J2.9, U19.19
A_REG_00: U19.9, U23.6
A_REG_01: U19.8, U23.5
A_REG_02: U19.7, U23.4
A_REG_03: U19.6, U23.3
A_REG_04: U19.5, U21.6
A_REG_05: U19.4, U21.5
A_REG_06: U19.3, U21.4
A_REG_07: U19.2, U21.3
A_SEG: U7.18, U10.7, U12.7, U14.7, U16.7
BUS_00: J4.8, U4.18, U6.3, U15.2, U19.11, U23.11
BUS_01: J4.7, U4.17, U6.4, U15.3, U19.12, U23.12
BUS_02: J4.6, U4.14, U6.5, U15.4, U19.13, U23.13
BUS_03: J4.5, U4.13, U6.6, U15.5, U19.14, U23.14
BUS_04: J4.4, U4.8, U9.3, U15.6, U19.15, U21.11
BUS_05: J4.3, U4.7, U9.4, U15.7, U19.16, U21.12
BUS_06: J4.2, U4.4, U9.5, U15.8, U19.17, U21.13
BUS_07: J4.1, U4.3, U9.6, U15.9, U19.18, U21.14
B_SEG: U7.17, U10.6, U12.6, U14.6, U16.6
CLOCK: J2.12, J3.2, U2.2, U6.2, U9.2, U21.7, U23.7
C_SEG: U7.16, U10.4, U12.4, U14.4, U16.4
DISPLAY_DIGIT_00: U1.6, U1.14, U3.2, U7.25
DISPLAY_DIGIT_01: U1.10, U3.3, U7.24
DISPLAY_HEX: J6.3, R2.2, U7.23
DISPLAY_IN: J6.2, U2.1
DISPLAY_RATE: U1.1, U5.3
DISPLAY_SIGNED: J6.1, R1.2, SW1.2, U7.21
DP_SEG: U7.19, U10.5, U12.5, U14.5, U16.5
D_SEG: U7.15, U10.2, U12.2, U14.2, U16.2
E_SEG: U7.13, U10.1, U12.1, U14.1, U16.1
F_SEG: U7.12, U10.9, U12.9, U14.9, U16.9
GND: C1.2, C2.1, C3.2, J1.1, J8.1, R1.1, R2.1, RN1.1, U1.13, U2.7, U3.1, U3.8, U4.10, U5.1, U6.8, U7.1, U7.2, U7.14, U7.20, U7.22, U7.26, U9.8, U15.1, U15.10, U19.10, U21.1, U21.2, U21.8, U23.1, U23.2, U23.8
G_SEG: U7.11, U10.10, U12.10, U14.10, U16.10
unnamed: BAR1.13, RN1.9
unnamed: BAR1.14, RN1.8
unnamed: BAR1.15, RN1.7
unnamed: BAR1.16, RN1.6
unnamed: BAR1.17, RN1.5
unnamed: BAR1.18, RN1.4
unnamed: BAR1.19, RN1.3
unnamed: BAR1.20, RN1.2
unnamed: C2.2, R3.2, U5.2, U5.6
unnamed: C3.1, U5.5
unnamed: R3.1, R4.1, U5.7
unnamed: U2.3, U4.11
unnamed: U4.2, U7.3
unnamed: U4.5, U7.4
unnamed: U4.6, U7.5
unnamed: U4.9, U7.6
unnamed: U4.12, U7.7
unnamed: U4.15, U7.8
unnamed: U4.16, U7.9
unnamed: U4.19, U7.10
unnamed: U6.15, U9.10
PC_00: BAR1.8, U9.11, U15.18
PC_01: BAR1.7, U9.12, U15.17
PC_02: BAR1.6, U9.13, U15.16
PC_03: BAR1.5, U9.14, U15.15
PC_04: BAR1.4, U6.11, U15.14
PC_05: BAR1.3, U6.12, U15.13
PC_06: BAR1.2, U6.13, U15.12
PC_07: BAR1.1, U6.14, U15.11
PC_CARRY_OUT: J5.4, U9.15
PC_CE: J5.3, U6.7, U6.10
PC_JUMP: J5.1, U6.9, U9.9
PC_OUT: J5.2, U15.19
RESET: J2.11, J3.1, U4.1, U6.1, U9.1, U21.15, U23.15
SIGN_DISPLAY: U3.7, U10.3, U10.8
VCC: C1.1, J1.2, J8.2, R4.2, SW1.1, U1.2, U1.3, U1.4, U1.5, U1.7, U1.8, U1.9, U1.12, U1.16, U2.14, U3.16, U4.20, U5.8, U6.16, U7.27, U7.28, U9.7, U9.16, U15.20, U19.1, U19.20, U21.16, U23.16
